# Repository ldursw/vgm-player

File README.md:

# VGM Player

This project allows VGM (Video Game Music) files from Sega Master System, Sega Game Gear,
and Sega Mega Drive/Genesis to be played on real hardware using the YM2612 sound chip and
the Teensy 3.6 board.

## Features

- Support for Master System, Game Gear, Mega Drive/Genesis
- Standalone player using the SD Card slot
- Can be controlled by a computer using the USB port
- Correct volume for PSG and FM
- Integration with emulators available
- Supports emulated and discrete SN76489
- Uses the Mega Amp circuit for amplification
- Hardware support for Teensy 3.6 and Arduino Due
- Player support for Windows and Linux (experimental)

## Supported boards

| Board | SD Card | Stream | Real PSG | Emulated PSG |
| --- | --- | --- | --- | --- |
| Teensy 3.6 | ✔️ | ✔️ | ✔️ | ✔️ |
| Arduino Due | ❔ | ✔️ | ✔️ | ✔️ |

✔️ Fully supported  
❔ Not tested  

## Demo
- [Instruction streaming from PC](https://www.youtube.com/watch?v=saAEF2lk2_Y)
- [Emulator with hardware sound](https://www.youtube.com/watch?v=Mupbj-XCC5c)
- [44.1kHz playback](https://www.youtube.com/watch?v=DkkqFxyVbDQ)
- [Music recordings](https://www.youtube.com/watch?v=EpjxUjE8uks)

## Difference between other implementations

### PSG

One of the biggest differences between this project and other implementations is that
an emulated PSG is used instead of the discrete SN76489. It is
[widely known](https://www.smspower.org/Development/SN76489#TheLinearFeedbackShiftRegister)
that the Sega version has some differences mainly in the noise channel.

For example, most games get a [weird artifact](https://gitcdn.link/cdn/ldursw/vgm-player/main/assets/panicpuppet-discrete.ogg) instead
of the [expected noise channel](https://gitcdn.link/cdn/ldursw/vgm-player/main/assets/panicpuppet-emulated.ogg).
After Burner II has a constant tone on a [discrete chip](https://gitcdn.link/cdn/ldursw/vgm-player/main/assets/afterburner-discrete.ogg)
whereas [on emulation](https://gitcdn.link/cdn/ldursw/vgm-player/main/assets/afterburner-emulated.ogg) it sounds right.

When using an emulated PSG the microcontroller will emulate the chip and the output is
sent to the `DAC0` pin at 44.1 kHz.

If you want to use a discrete PSG anyway, all you have to do is uncomment `-DUSE_REAL_PSG`
on `hardware/platformio.ini`, connect the `D0..D7` lines from the shift register to the
SN76489 and connect `/WE` to pin 29 though a voltage converter.

### Remote control

Another difference is that the hardware can be controlled via a companion application
written in .NET Core that accepts a generic input class and sends to the hardware via
USB and also displays the current state on screen.

There are 3 available input methods. `VgmFile` reads standard `.vgm` and `.vgz` files.
`VgmPipe` creates a named pipe `vgmstream` that accepts commands from other applications,
such as emulators. `VgmPCM` streams 44.1 kHz signed 8-bit mono PCM files to the chip.

## Compiling and Running the project

To compile the code for the hardware you will need [PlatformIO](https://platformio.org/).
You can use the CLI or an IDE with extension support such as Visual Studio Code. After
installing PlatformIO just open the `hardware` directory and upload the code to the board.

To compile the player application you will need the
[.NET Core SDK](https://dotnet.microsoft.com/download). You can use the CLI or an IDE
such as Visual Studio Community or Visual Studio Code. On Linux you may have to install
the `libSDL2` package.

## License

All files in this repository are licensed under GNU General Public License Version 3.

## Credits

Thank you very much for all these awesome people

- Maxim - PSG emulation code
- Dave, Maxim, Valley Bell - VGM Format
- zamaz - [DGen/SDL emulator](https://sourceforge.net/projects/dgen/files/dgen/1.33/)
- Softdev, Eke-Eke - [Genesis Plus GX emulator](https://github.com/ekeeke/Genesis-Plus-GX)
- Ace, Villahed94 - [Mega Amp](https://www.sega-16.com/forum/showthread.php?26568-Introducing-the-Mega-Amp-The-universal-Genesis-audio-circuit)
- Stephane-D - [XGM Tool and XGM Player](https://github.com/Stephane-D/SGDK/tree/master/sample/xgm-player)
- SDL Community - [SDL](https://www.libsdl.org/)
- greiman - [SdFat library](https://github.com/greiman/SdFat)
- ivanseidel - [DueTimer library](https://github.com/ivanseidel/DueTimer)

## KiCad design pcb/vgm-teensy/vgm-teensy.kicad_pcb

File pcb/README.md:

## VGM Player PCB

Schematic, KiCad 6 project and gerber files for the VGM player using Teensy 3.6.

This is a 2-layer board made with tolerances compatible with JLCPCB.

## Bill of materials

| Quantity | Item                                   | Notes                         |
|----------|----------------------------------------|-------------------------------|
| 55       | Femake header socket                   | 48 for teensy, 7 for SI5351   |
| 10       | Breakaway male headers                 | 4 for the SX1308 module       |
| 4        | 100k SMD 0805 resistor                 |                               |
| 3        | 10uF SMD 0805 ceramic capacitor        |                               |
| 3        | 0.1uF SMD 0805 ceramic capacitor       |                               |
| 2        | 47pF THT 2.54' pitch ceramic capacitor | Can be replaced with SMD 0805 |
| 2        | 1uF, 16V electrolytic capacitor        |                               |
| 2        | 10uF, 25V electrolytic capacitor       |                               |
| 2        | 2.2k SMD 0805 resistor                 |                               |
| 2        | 4.7k SMD 0805 resistor                 |                               |
| 2        | Jumper cap                             |                               |
| 1        | 2.1mm Barrel Jack                      |                               |
| 1        | SX1308 Step-Up Converter               |                               |
| 1        | 7805 Regulator, TO-220                 |                               |
| 1        | 100uH Inductor CD105                   |                               |
| 1        | Teensy 3.6 with pins                   |                               |
| 1        | TXS0108E, TSSOP-20                     |                               |
| 1        | 24-pin DIP socket, wide                |                               |
| 1        | 3.5mm headphone jack, female           |                               |
| 1        | AMS1117-3.3 regulator                  |                               |
| 1        | 330r SMD 0805 resistor                 |                               |
| 1        | 470r SMD 0805 resistor                 |                               |
| 1        | 680r SMD 0805 resistor                 |                               |
| 1        | TL072 op-amp                           |                               |
| 1        | Adafruit SI5351 Clock Generator        |                               |
| 1        | 74HC595 shift register, SOP-16         |                               |

## Assembly instructions

- Solder all components but leave the YM2612, Teensy, and clock generator disconnected.
- Make sure the jumper JP2 (near the 7805) is removed.
- Set the jumper J3 (near the barrel jack) to `* [* *] *` (EXT to center pin).
- Apply 5V to the barrel jack, center positive.
- Adjust the step-up module until it reaches 8V at the output.
- Remove power.
- Add a jumper to JP2 and move J3 to `[* *] * *` (VIN to center pin).
- Plug the Teensy, YM2612, and the clock generator into the board.
- Plug the headphone jack to line-in or a powered speaker.
- Connect the Teensy to the PC with an USB cable.
- Use the player in this repo to play music from file or emulator.

## 3D Render

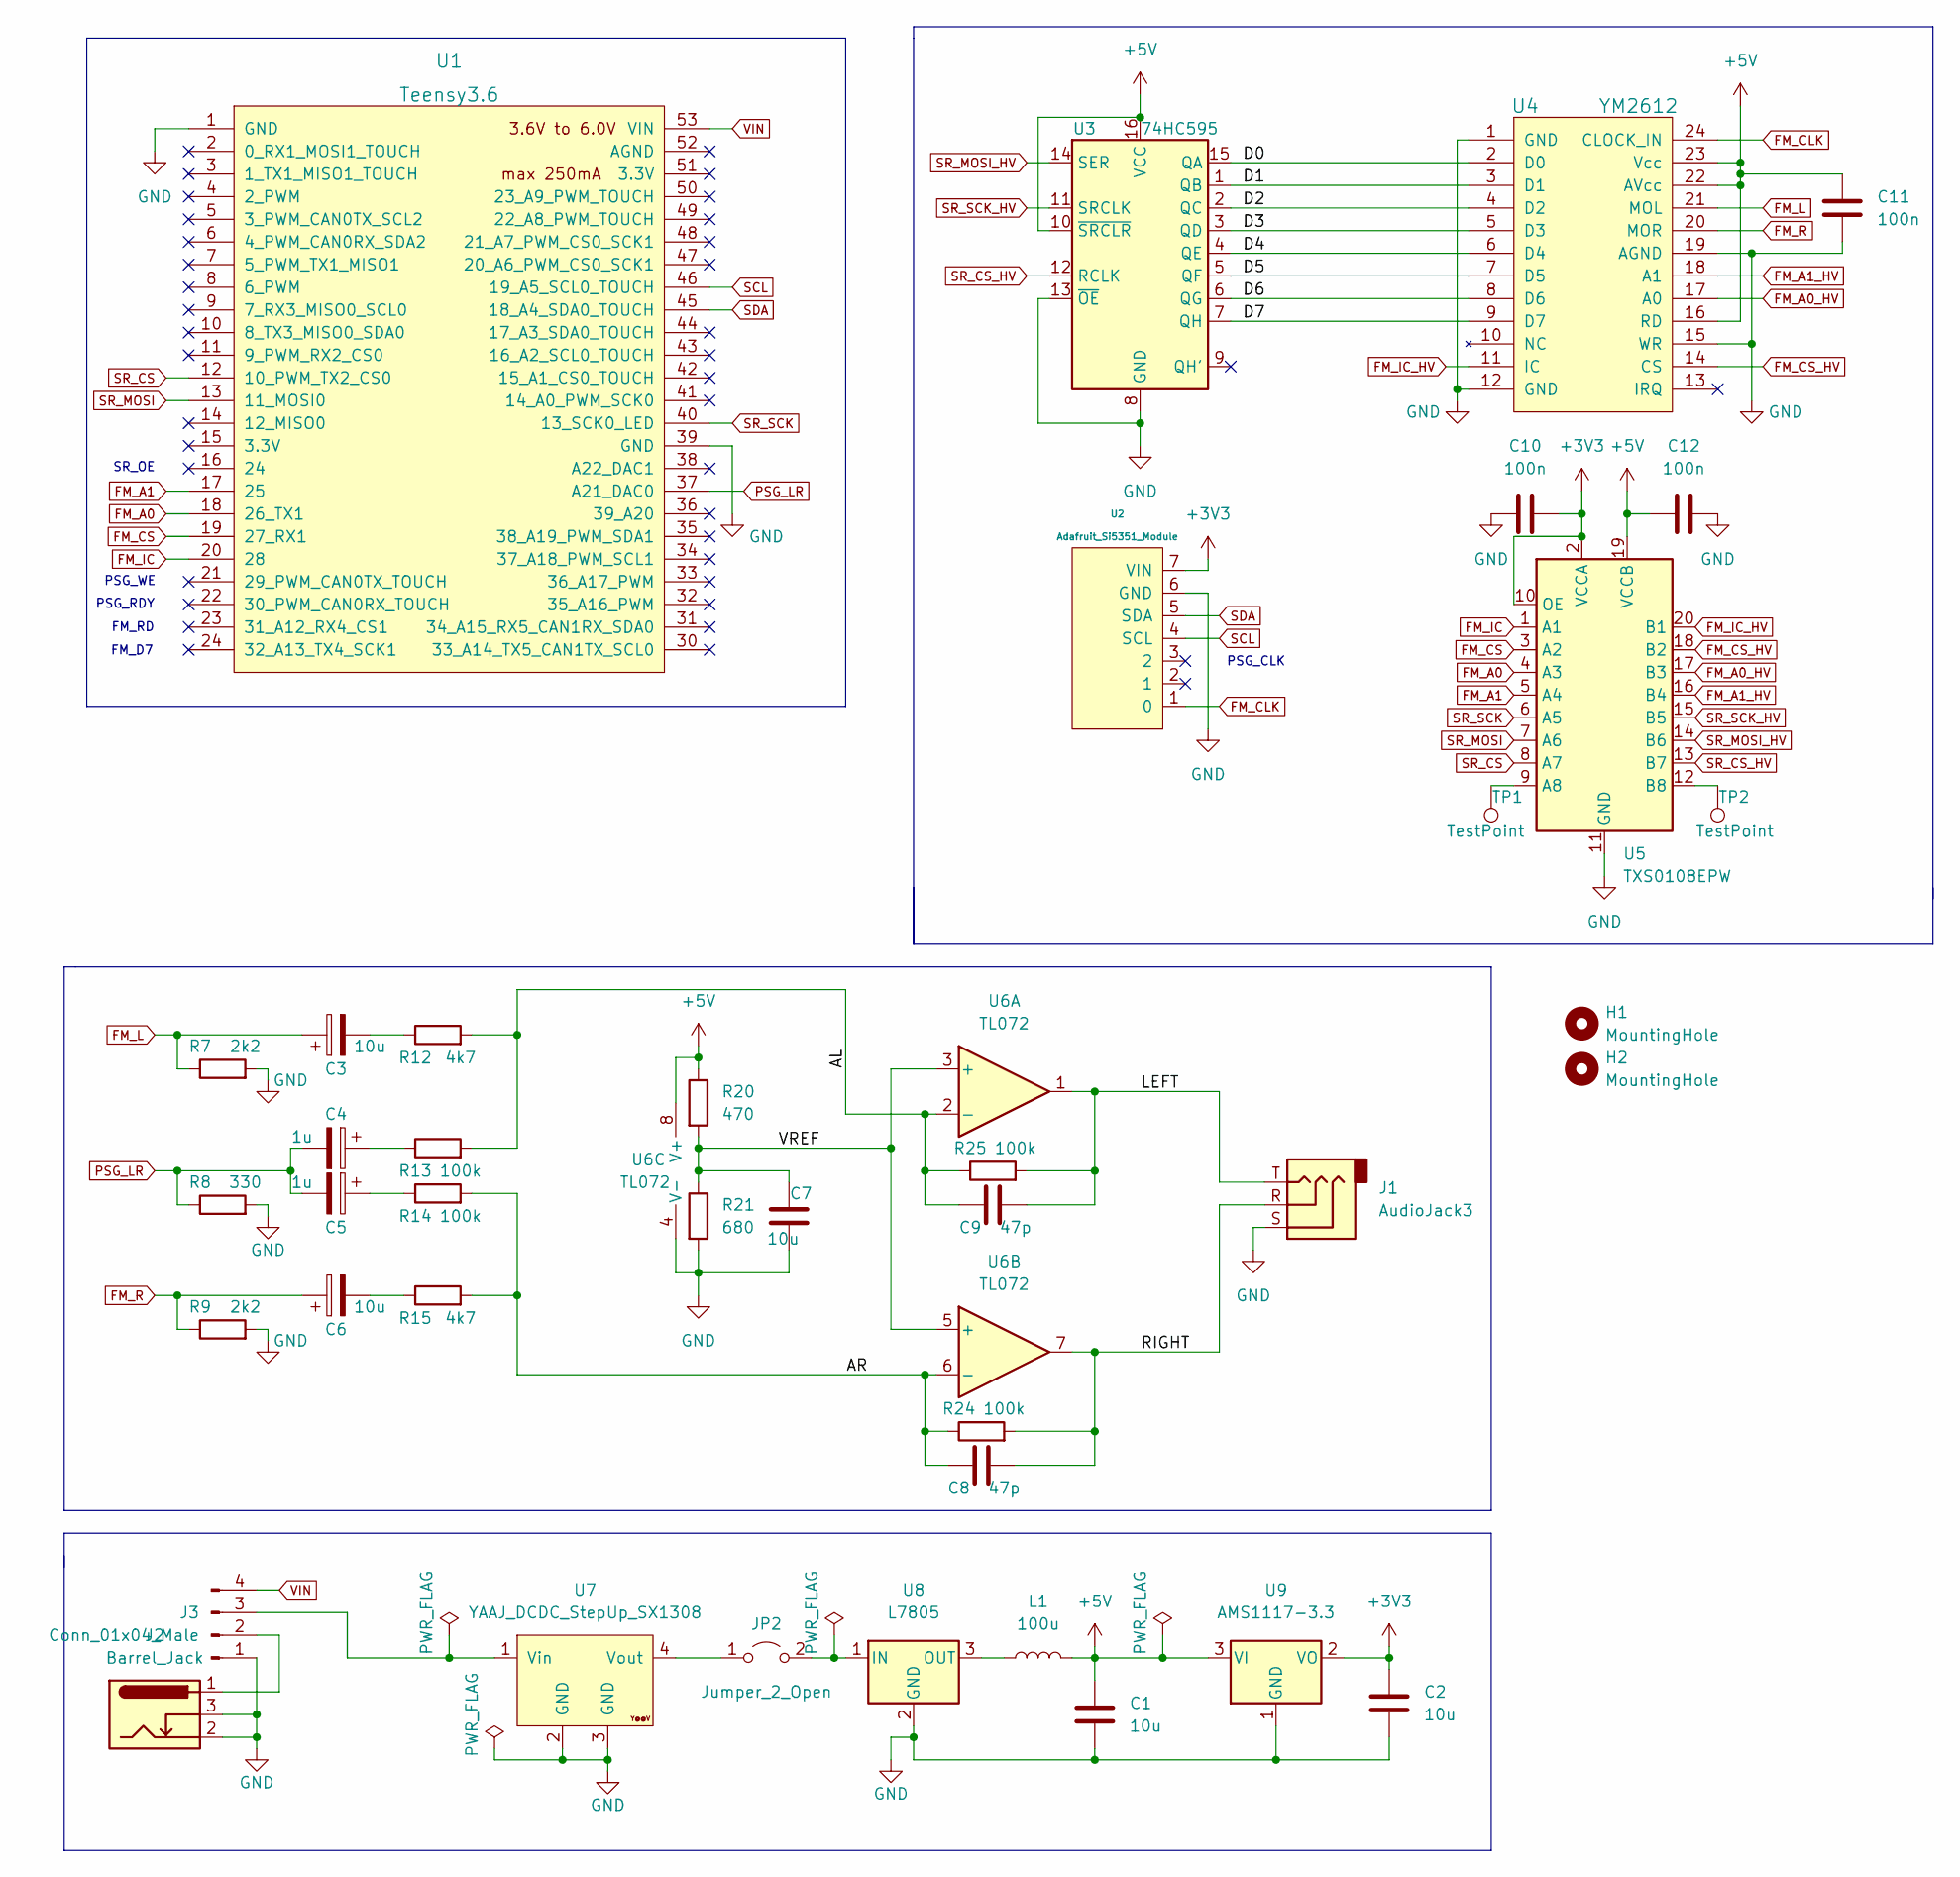
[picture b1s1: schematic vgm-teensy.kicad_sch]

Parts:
C1, C2, C7: 10u; C_0805_2012Metric_Pad1.18x1.45mm_HandSolder
C3, C6: 10u; CP_Radial_D5.0mm_P2.50mm
C4, C5: 1u; CP_Radial_D5.0mm_P2.50mm
C8, C9: 47p; C_Disc_D3.0mm_W1.6mm_P2.50mm
C10, C11, C12: 100n; C_0805_2012Metric_Pad1.18x1.45mm_HandSolder
H1, H2: MountingHole; MountingHole_3.2mm_M3
J1: AudioJack3; Jack_3.5mm_Lumberg_1503_07_Horizontal
J2: Barrel_Jack; BarrelJack_Horizontal
J3: Conn_01x04_Male; PinHeader_1x04_P2.54mm_Vertical
JP2: Jumper_2_Open; PinHeader_1x02_P2.54mm_Vertical
L1: 100u; Choke_CD105
R7, R9: 2k2; R_0805_2012Metric_Pad1.20x1.40mm_HandSolder
R8: 330; R_0805_2012Metric_Pad1.20x1.40mm_HandSolder
R12, R15: 4k7; R_0805_2012Metric_Pad1.20x1.40mm_HandSolder
R13, R14, R24, R25: 100k; R_0805_2012Metric_Pad1.20x1.40mm_HandSolder
R20: 470; R_0805_2012Metric_Pad1.20x1.40mm_HandSolder
R21: 680; R_0805_2012Metric_Pad1.20x1.40mm_HandSolder
TP1, TP2: TestPoint; TestPoint_Pad_D1.0mm
U1: Teensy3.6; Teensy35_36
U2: Adafruit_Si5351_Module
U3: 74HC595; SOP-16_3.9x9.9mm_P1.27mm
U4: YM2612; DIP-24_W15.24mm_Socket
U5: TXS0108EPW; TSSOP-20_4.4x6.5mm_P0.65mm
U6: TL072; SOIC-8_3.9x4.9mm_P1.27mm
U7: YAAJ_DCDC_StepUp_SX1308
U8: L7805; TO-220-3_Vertical
U9: AMS1117-3.3; SOT-223-3_TabPin2

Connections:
+3V3: C2.1, C10.2, U2.7 (VIN), U5.2 (VCCA), U5.10 (OE), U9.2 (VO)
+5V: C1.1, C11.1, C12.1, L1.2, R20.1, U3.10 (~SRCLR), U3.16 (VCC), U4.16 (RD), U4.22 (AVcc), U4.23 (Vcc), U5.19 (VCCB), U6.8 (V+), U9.3 (VI)
/AL: C9.1, R12.2, R13.2, R25.1, U6.2 (-)
/AR: C8.1, R14.2, R15.2, R24.1, U6.6 (-)
/D0: U3.15 (QA), U4.2 (D0)
/D1: U3.1 (QB), U4.3 (D1)
/D2: U3.2 (QC), U4.4 (D2)
/D3: U3.3 (QD), U4.5 (D3)
/D4: U3.4 (QE), U4.6 (D4)
/D5: U3.5 (QF), U4.7 (D5)
/D6: U3.6 (QG), U4.8 (D6)
/D7: U3.7 (QH), U4.9 (D7)
/LEFT: C9.2, J1.T, R25.2, U6.1
/RIGHT: C8.2, J1.R, R24.2, U6.7
/VREF: C7.1, R20.2, R21.1, U6.3 (+), U6.5 (+)
FM_A0: U1.18 (26_TX1), U5.4 (A3)
FM_A0_HV: U4.17 (A0), U5.17 (B3)
FM_A1: U1.17 (25), U5.5 (A4)
FM_A1_HV: U4.18 (A1), U5.16 (B4)
FM_CLK: U2.1 (0), U4.24 (CLOCK_IN)
FM_CS: U1.19 (27_RX1), U5.3 (A2)
FM_CS_HV: U4.14 (CS), U5.18 (B2)
FM_IC: U1.20 (28), U5.1 (A1)
FM_IC_HV: U4.11 (IC), U5.20 (B1)
FM_L: C3.1, R7.1, U4.21 (MOL)
FM_R: C6.1, R9.1, U4.20 (MOR)
GND: C1.2, C2.2, C7.2, C10.1, C11.2, C12.2, J1.S, J2.2, J2.3, J3.1, R7.2, R8.2, R9.2, R21.2, U1.1 (GND), U1.39 (GND), U2.6 (GND), U3.8 (GND), U3.13 (~OE), U4.1 (GND), U4.12 (GND), U4.15 (WR), U4.19 (AGND), U5.11 (GND), U6.4 (V-), U7.2 (GND), U7.3 (GND), U8.2 (GND), U9.1 (GND)
unnamed: C3.2, R12.1
unnamed: C4.1, R13.1
unnamed: C5.1, R14.1
unnamed: C6.2, R15.1
unnamed: J2.1, J3.2
unnamed: J3.3, U7.1 (Vin)
unnamed: JP2.1 (A), U7.4 (Vout)
unnamed: JP2.2 (B), U8.1 (IN)
unnamed: L1.1, U8.3 (OUT)
unnamed: TP1.1, U5.9 (A8)
unnamed: TP2.1, U5.12 (B8)
PSG_LR: C4.2, C5.2, R8.1, U1.37 (A21_DAC0)
SCL: U1.46 (19_A5_SCL0_TOUCH), U2.4 (SCL)
SDA: U1.45 (18_A4_SDA0_TOUCH), U2.5 (SDA)
SR_CS: U1.12 (10_PWM_TX2_CS0), U5.8 (A7)
SR_CS_HV: U3.12 (RCLK), U5.13 (B7)
SR_MOSI: U1.13 (11_MOSI0), U5.7 (A6)
SR_MOSI_HV: U3.14 (SER), U5.14 (B6)
SR_SCK: U1.40 (13_SCK0_LED), U5.6 (A5)
SR_SCK_HV: U3.11 (SRCLK), U5.15 (B5)
VIN: J3.4, U1.53 (VIN)

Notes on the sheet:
FM_D7
PSG_WE
PSG_CLK
PSG_RDY
FM_RD
SR_OE

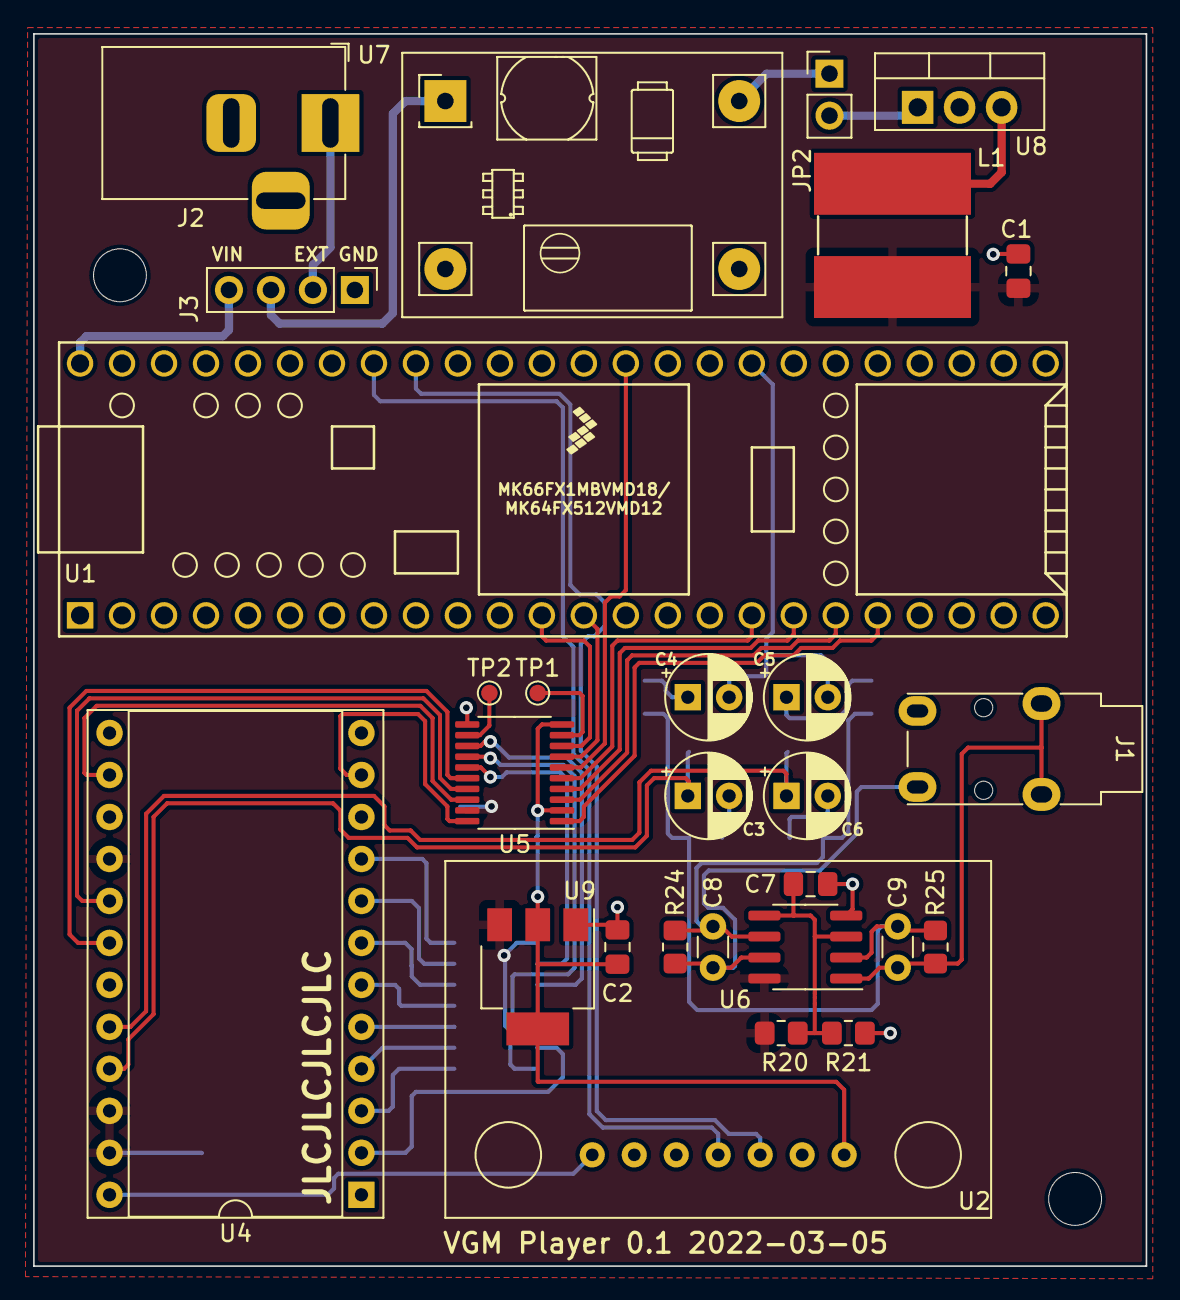
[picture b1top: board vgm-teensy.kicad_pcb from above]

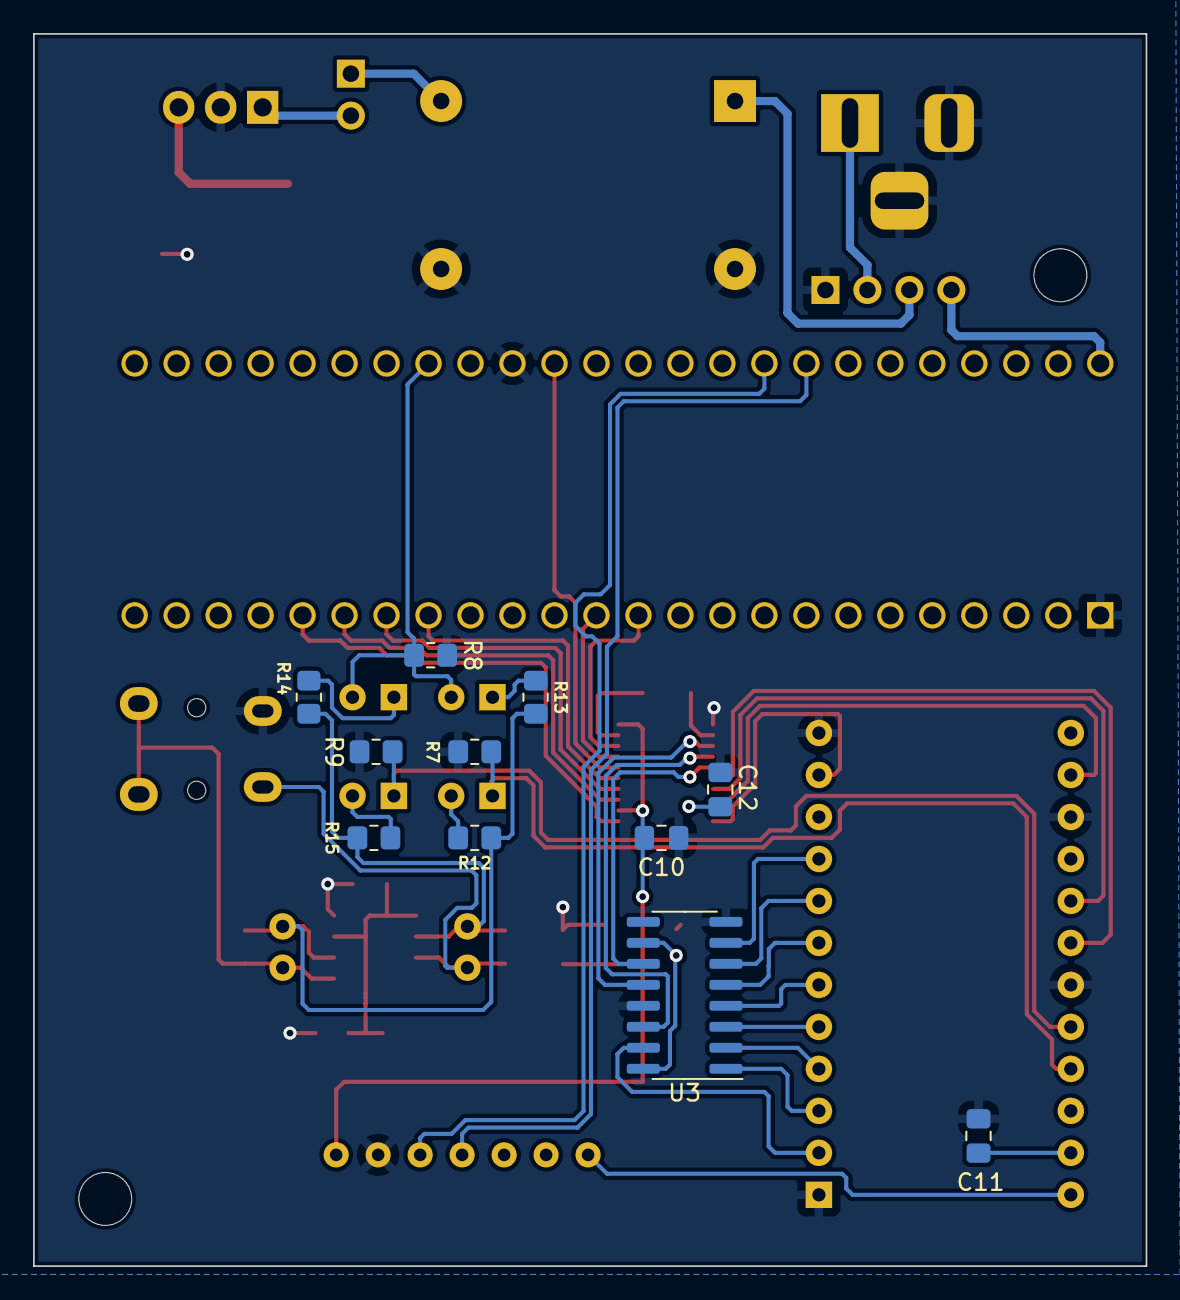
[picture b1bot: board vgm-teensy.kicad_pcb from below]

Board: 2 copper layers, 67.3 x 74.5 mm, 41 parts (11 on the bottom side), 48 nets.

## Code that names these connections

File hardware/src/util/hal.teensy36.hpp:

#define SdFatCls SdFatSdio
#define SerialUSB Serial

#define PSG_DAC A21
#define PSG_ATTENUATION 6

#define FM_A1   25
#define FM_A0   26
#define FM_WR   27
#define FM_IC   28
#define PSG_WE  29
#define PSG_RDY 30
#define FM_RD   31
#define FM_D7   32

#include <Arduino.h>

inline __attribute__((always_inline)) void enableDAC0()
{
    pinMode(PSG_DAC, OUTPUT);
    analogWriteResolution(12);
}

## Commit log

2020-08-21 Add LICENSE
2020-08-21 Add Initial Commit
2020-08-23 Remove FmOptimizer
2020-08-23 Remove unused commands
2020-08-23 Add SDL2.dll
2020-08-23 Change OpenSerial signature to return Stream
2020-08-23 Fix calculation for zero wait
2020-08-23 Change VgmData to enable PcmRamWrite
2020-08-23 Add linux support in VgmPlayer
2020-08-23 Add DGen patch
2020-08-24 Add instructions on how to patch the emulator
2020-08-25 Simplify WaitSamples
2020-08-25 Clean up the code
2020-08-25 Change uint to VgmInstruction
2020-08-25 Improve readability at Dispatcher::setup
2020-08-25 Simplify Dispatcher::enqueue
2020-08-25 Add comment
2020-08-25 Remove Windows-specific options
2020-08-25 Enable nullable reference types
2020-08-26 Change uint8_t to union type
2020-08-26 Change waitSamples to uint32
2020-08-26 Simplify switch statement
2020-08-26 Remove unnecessary code
2020-08-26 Replace inline function with loop
2020-08-29 Fix endianness
2020-08-30 Change shift register function to SPI class
2020-08-30 Add panning instruction to PCM
2020-08-30 Add reset instruction when the emulator is closed
2020-08-30 Move register render to own function
2020-08-30 Move PSG render to own function
2020-08-30 Add FM graph
2020-08-30 Disable register view
2020-08-30 Add relative position to register view
2020-08-30 Change elements position to match XGM
2020-08-30 Set window as resizable
2020-08-30 Change audio link to html page
2020-08-30 Update player screenshot
2020-08-30 Add polymorphic screen rendering
2020-08-30 Move audio code to AudioQueue
2020-08-30 Rename .h to .hpp
2020-08-30 Add support for Arduno Due
2020-08-30 Add SerialUSB to hal
2020-08-30 Fix frequency position
2020-08-30 Optimize background rect
2020-08-30 Add SPDX license
2020-08-30 Remove whitespace
2020-08-30 Add wait for SerialUSB
2020-08-31 Rename VgmReader to VgmPlayer
2020-08-31 Fix code style
2020-08-31 Fix serial wait on teensy
2020-09-01 Cleanup code
2020-09-05 Remove WAIT_SERIAL
2020-09-05 Change float comparison to bool
2020-09-05 Add PSG attenuation for Arduino Due
2020-09-05 Add conditional for longer wait on Teensy
2020-09-05 Add DAC support for Arduino Due
2020-09-05 Move HAL to one file per platform
2020-09-05 Add Arduino Due schematics
2020-09-05 Fix PSG optimization
2020-09-05 Change variable type to cstdint
2020-09-05 Add int fallback for SoftFP
2020-09-06 Change circular buffer implementation
2020-09-06 Add interrupt guard on reset
2020-09-06 Move PSG emulation to top
2020-09-06 Add interrupt guards
2020-09-06 Update PSG attenuation
2021-04-23 Add constraint to Map
2021-04-23 Fix sustain level
2021-04-23 Improve position for frequency bar
2021-04-23 Simplify volume calculation
2021-04-23 Add fixed point to PSG emulator
2021-04-23 Add delay to FM
2021-04-24 Change variable length
2021-04-24 Simplify latched register
2021-04-24 Move updateChannel to calculateChannel
2021-07-10 Fix ExecutionEngineException on close
2021-07-10 Remove UTF-8 BOM
2021-07-10 Fix discard
2021-07-13 Split timer implementations
2022-02-07 Fix compilation
2022-02-07 Increase speed on ShiftRegister
2022-02-07 Add initial commit for Raspberry Pi Pico
2022-02-07 Add register view to GUI
2022-02-07 Add check for invalid addresses
2022-02-07 Fix audio demo links
2022-03-06 Increase serial clock
2022-03-06 Change packet length to 4 bytes
2022-03-06 Add FM filter
2022-03-06 Add screen clear on reset
2022-03-06 Fix data offset
2022-03-06 Simplify code
2022-03-06 Improve PCM graph
2022-03-07 Fix freeze on emulator when PCM starts
2022-05-07 Fix artifact on off-center sample
2022-05-07 Fix wrong timing
2022-05-07 Refactor file input class
2022-05-07 Change GUI layout
2022-05-07 Increase wait for FM commands
2022-05-07 Change player project to .NET 5
2022-05-14 Add filters
2022-05-14 Remove heap allocation
2022-05-14 Add filter for timer data
2022-05-14 Add key on-off filter
2022-05-14 Add frequency filter
2022-05-15 Fix artifacts on VgmPipe
2022-05-15 Add PCB
